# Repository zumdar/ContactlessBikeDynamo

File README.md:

# Contactless Bicycle Dynamo using Eddy Currents

This is a [certified Open Source](https://certification.oshwa.org/us002771.html) small electrical generator that creates enough current to power a small bicycle light while your wheel is spinning. 

# Description

The design files here include the physical design files for the Dynamo and the LED light, as well as a custom PCB for the LED light which is a simple voltage rectifier doubler and choice of red or white led. 

If you would like to make this project:
- print off the files in:
  -  \Mechanical\Components\STLs\Final STL
- acquire parts in the 
- aquire tools in the 
- follow instructions in the 

This project started off with a desire to be a workshop I could host to show an interesting way to generate electricity and power a bike light without needing a battery. 

Here are the workshop slides:
https://docs.google.com/presentation/d/1txSlyZcSNcTIk4scu_-NPuIz-HN-7od_rSDEqWW2YtM/edit?usp=sharing

# Technical 

## Physical Design Files
The parts are labelled as follows:

- P001-B100	-	Square Dynamo
- P001-B101	-	Dynamo Cover
- P001-B102	-	Magnet Holder Ring
- P001-B103	-	M5 Bearing Adaptor
- P001-B104	-	Fork Bracket
- P001-B105	-	PCB Cover
- P001-B106	-	LED Light Mount

There is also an assembly of the Dynamo labelled:

- P001-B001	-	Dynamo
## PCB Design files

The PCB contains red and white LEDs which can be selected by doing a solder bridge while assembling. 

You can't use both at the same time. If you solder both, only the Red LED will light (it has a lower forward voltage). 

The LED PCB design can be found in:
- \Electrical\Dyno_LED_PCB

# Acknowledgments

Thank you to:
Lucas Ray, Clara Caspard, and YJ Rodrigues for helping develop this! 

# License
This is an certified [open source project](https://certification.oshwa.org/us002771.html)!

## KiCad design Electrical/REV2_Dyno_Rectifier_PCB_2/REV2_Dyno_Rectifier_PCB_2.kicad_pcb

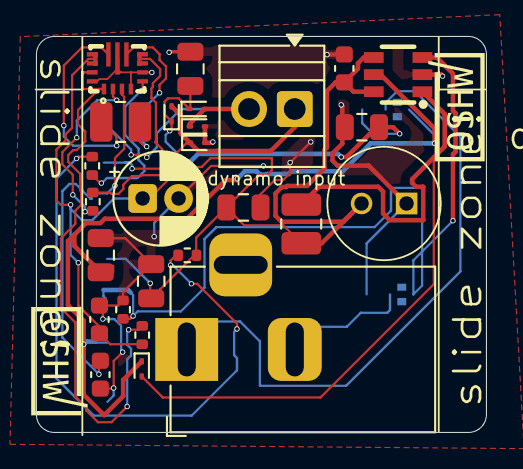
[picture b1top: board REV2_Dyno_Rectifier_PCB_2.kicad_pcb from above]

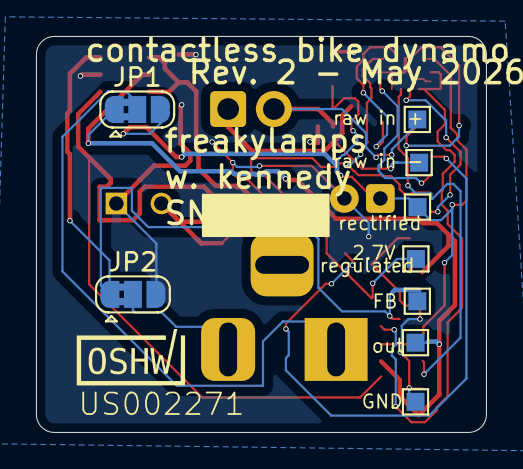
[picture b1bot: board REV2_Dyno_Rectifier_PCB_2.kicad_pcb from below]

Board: 2 copper layers, 25.0 x 22.0 mm, 35 parts (9 on the bottom side), 17 nets.

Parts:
C1: 100u; CP_Radial_D5.0mm_P2.00mm
C2, C8, C9, C10: 10uF; C_0805_2012Metric
C3, C5: 10uF; C_0603_1608Metric
C4: 100nF; C_0603_1608Metric
C6: 47uF; C_0805_2012Metric
C7: 1F - 2.7V; supercapacitor - 4mm diameter
D1, D2, D3, D4, D5: D_Schottky; D_SOD-923
J1: Dynamo Input; TerminalBlock_Xinya_XY308-2.54-2P_1x02_P2.54mm_Horizontal
J2: Barrel_Jack_MountingPin; BarrelJack_Horizontal
JP1, JP2: SolderJumper_3_Bridged12; SolderJumper-3_P1.3mm_Bridged2Bar12_RoundedPad1.0x1.5mm
L1: 1.5uH; L_1008_2520Metric
L2: 2.2uH; L_1008_2520Metric
R1: 10k; R_0402_1005Metric
R2: 360k; R_0402_1005Metric
R3: 150k; R_0402_1005Metric
R4: 100k; R_0402_1005Metric
R5: 1.8; R_0402_1005Metric
TP1, TP2, TP3, TP4, TP5, TP6, TP7: TestPoint; TestPoint_Pad_1.0x1.0mm
U1: TPS63070RNMR; TPS63070RNMR-2
U2: PAM2803AAF095; PAM2803_SOT-23-6_L2.9-W1.6-P0.95-LS2.8-BR

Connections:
2.7V: C5.1, C6.1, C7.1, C8.1, L2.1, R2.1, R4.1, TP4.1, U1.7 (Vout), U2.4 (SHDN#), U2.6 (VIN)
FB: JP2.1 (A), R5.1, TP5.1, U2.3 (FB)
GND: C1.2, C2.2, C3.2, C4.2, C5.2, C6.2, C7.2, C8.2, C9.2, C10.2, D1.2 (A), D2.2 (A), JP2.3 (B), R5.2, TP7.1, U1.4 (GND), U1.6 (FB2), U1.10 (PGND), U1.15 (Vsel), U2.2 (GND)
unnamed: D5.2 (A), L2.2, U2.1 (SW)
unnamed: R2.2, R3.1
unnamed: R1.2, U1.1 (PS/SYNC), U1.14 (EN)
unnamed: R3.2, U1.5 (FB)
unnamed: L1.1, U1.11 (L1)
unnamed: L1.2, U1.9 (L2)
unnamed: R4.2, U1.2 (PG)
unnamed: C4.1, U1.3 (Vaux)
Out_Sleeve: J2.2, JP2.2 (C)
Out_Tip: J2.1, JP1.2 (C)
Raw_Input_+: D1.1 (K), D3.2 (A), J1.2, TP1.1
Raw_Input_-: D2.1 (K), D4.2 (A), J1.1, TP2.1
Rectified: C1.1, C2.1, C3.1, C10.1, D3.1 (K), D4.1 (K), JP1.3 (B), R1.1, TP3.1, U1.12 (Vin)
V_out: C9.1, D5.1 (K), JP1.1 (A), TP6.1, U2.5 (VOUT)

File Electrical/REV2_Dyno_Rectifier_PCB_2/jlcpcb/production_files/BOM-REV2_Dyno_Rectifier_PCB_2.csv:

Comment,Designator,Footprint,LCSC,Quantity
1.5uH,L1,L_1008_2520Metric,C5339200,1
1.8,R5,R_0402_1005Metric,C2960794,1
100k,R4,R_0402_1005Metric,C25741,1
100nF,C4,C_0603_1608Metric,C14663,1
100u,C1,CP_Radial_D5.0mm_P2.00mm,C108360,1
10k,R1,R_0402_1005Metric,C25744,1
10uF,"C10,C2,C8,C9",C_0805_2012Metric,C440198,4
10uF,"C3,C5",C_0603_1608Metric,C96446,2
150k,R3,R_0402_1005Metric,C2909320,1
2.2uH,L2,L_1008_2520Metric,C394950,1
360k,R2,R_0402_1005Metric,C2909351,1
47uF,C6,C_0805_2012Metric,C16780,1
Barrel_Jack_MountingPin,J2,BarrelJack_Horizontal,C16214,1
D_Schottky,"D1,D2,D3,D4,D5",D_SOD-923,C2886012,5
Dynamo Input,J1,TerminalBlock_Xinya_XY308-2.54-2P_1x02_P2.54mm_Horizontal,C557685,1
PAM2803AAF095,U2,PAM2803_SOT-23-6_L2.9-W1.6-P0.95-LS2.8-BR,C55801,1
TPS63070RNMR,U1,TPS63070RNMR-2,C109322,1
1F - 2.7V,C7,supercapacitor - 4mm diameter,,1

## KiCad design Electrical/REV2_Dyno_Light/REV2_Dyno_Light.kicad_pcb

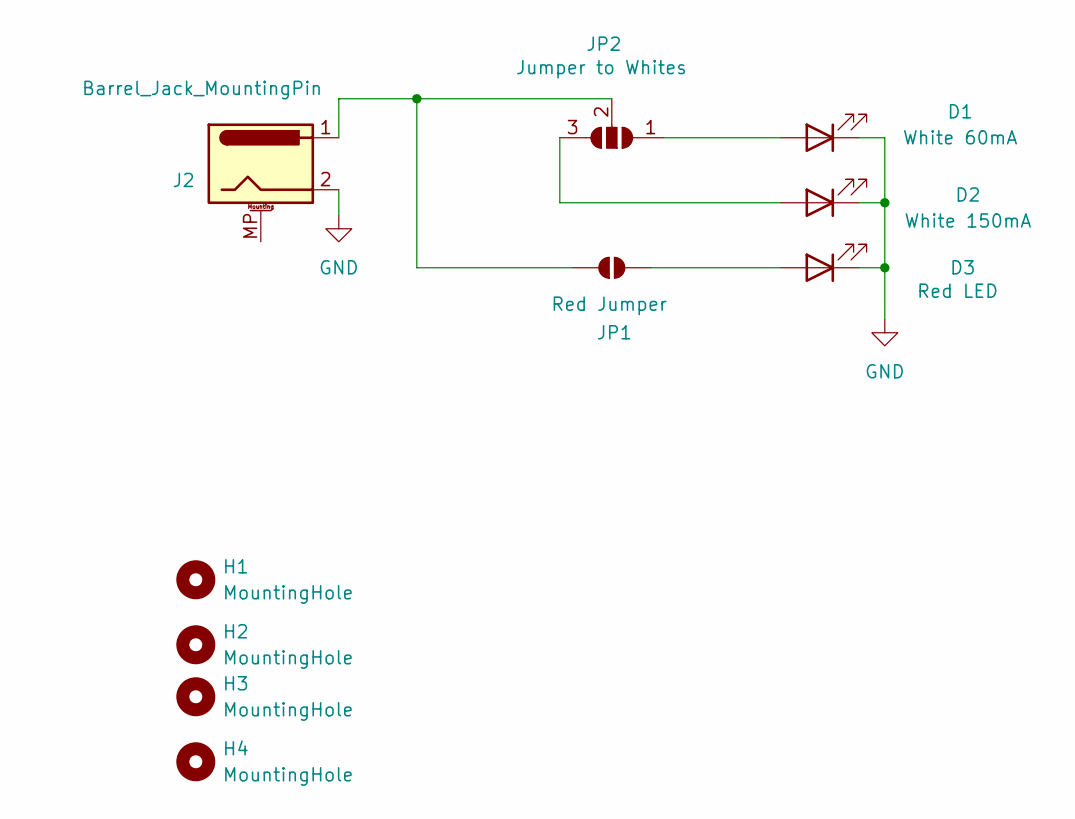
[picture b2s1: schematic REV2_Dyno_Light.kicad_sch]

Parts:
D1: White 60mA; LED_PLCC_2835; LCSC C210310
D2: White 150mA; LED_PLCC_2835; LCSC C210320
D3: Red LED; LED_PLCC_2835
H1, H2, H3, H4: MountingHole; MountingHole_3.2mm_M3
J2: Barrel_Jack_MountingPin; BarrelJack_Horizontal; LCSC C16214
JP1: Red Jumper; SolderJumper-2_P1.3mm_Open_TrianglePad1.0x1.5mm
JP2: Jumper to Whites; SolderJumper-3_P2.0mm_Open_TrianglePad1.0x1.5mm_NumberLabels

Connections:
GND: D1.1 (K), D2.1 (K), D3.1 (K), J2.2
unnamed: D1.2 (A), JP2.1 (A)
unnamed: D2.2 (A), JP2.3 (B)
unnamed: D3.2 (A), JP1.2 (B)
unnamed: J2.1, JP1.1 (A), JP2.2 (C)

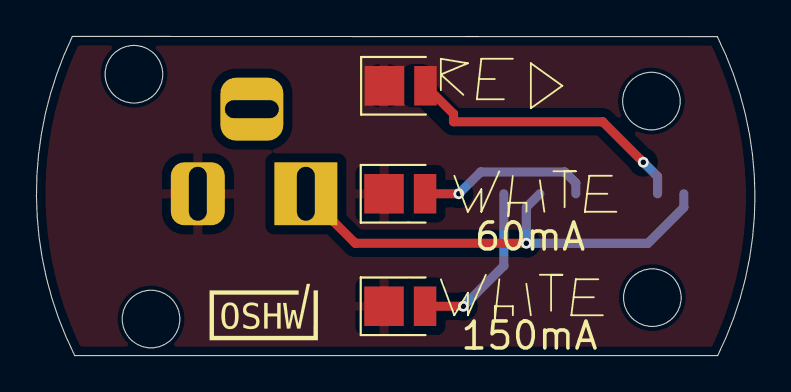
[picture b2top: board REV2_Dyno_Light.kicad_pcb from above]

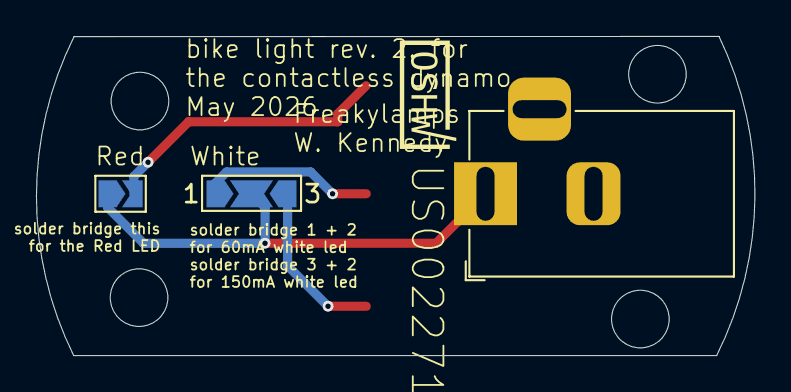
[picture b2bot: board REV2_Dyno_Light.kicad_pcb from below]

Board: 2 copper layers, 39.9 x 17.7 mm, 10 parts (3 on the bottom side), 5 nets.

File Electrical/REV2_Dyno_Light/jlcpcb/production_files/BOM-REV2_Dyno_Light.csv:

Comment,Designator,Footprint,LCSC,Quantity
Barrel_Jack_MountingPin,J2,BarrelJack_Horizontal,C16214,1
White 150mA,D2,LED_PLCC_2835,C210320,1
White 60mA,D1,LED_PLCC_2835,C210310,1
Red LED,D3,LED_PLCC_2835,,1

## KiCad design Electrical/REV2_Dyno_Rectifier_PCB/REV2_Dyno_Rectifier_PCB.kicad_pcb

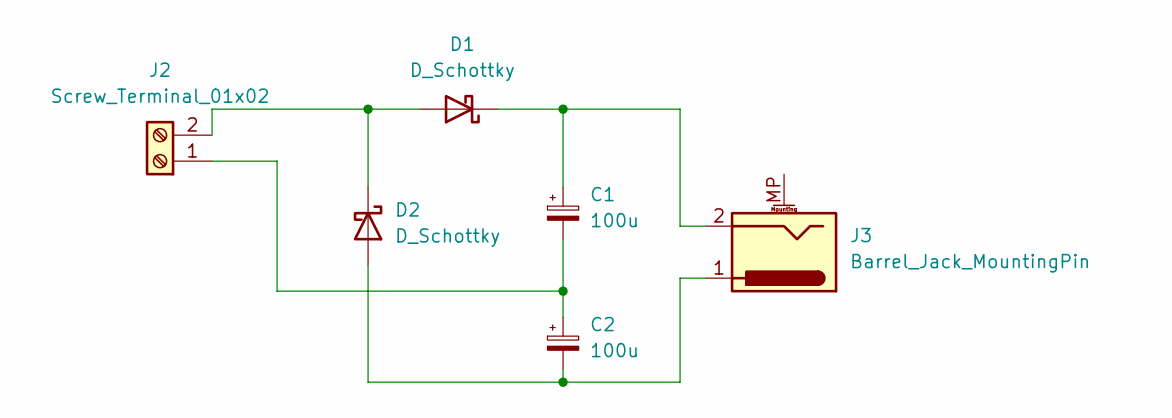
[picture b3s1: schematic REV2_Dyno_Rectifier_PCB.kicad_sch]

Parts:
C1, C2: 100u; CP_Elec_6.3x7.7; LCSC C3338
D1, D2: D_Schottky; D_SOD-123; LCSC C8570
J2: Screw_Terminal_01x02; TerminalBlock_Xinya_XY308-2.54-2P_1x02_P2.54mm_Horizontal; LCSC C557685
J3: Barrel_Jack_MountingPin; BarrelJack_Horizontal; LCSC C16214

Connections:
unnamed: D1.2 (A), D2.1 (K), J2.2
unnamed: C1.1, D1.1 (K), J3.2
unnamed: C2.2, D2.2 (A), J3.1
unnamed: C1.2, C2.1, J2.1

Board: 2 copper layers, 6 parts (0 on the bottom side), 4 nets, no tracks yet.

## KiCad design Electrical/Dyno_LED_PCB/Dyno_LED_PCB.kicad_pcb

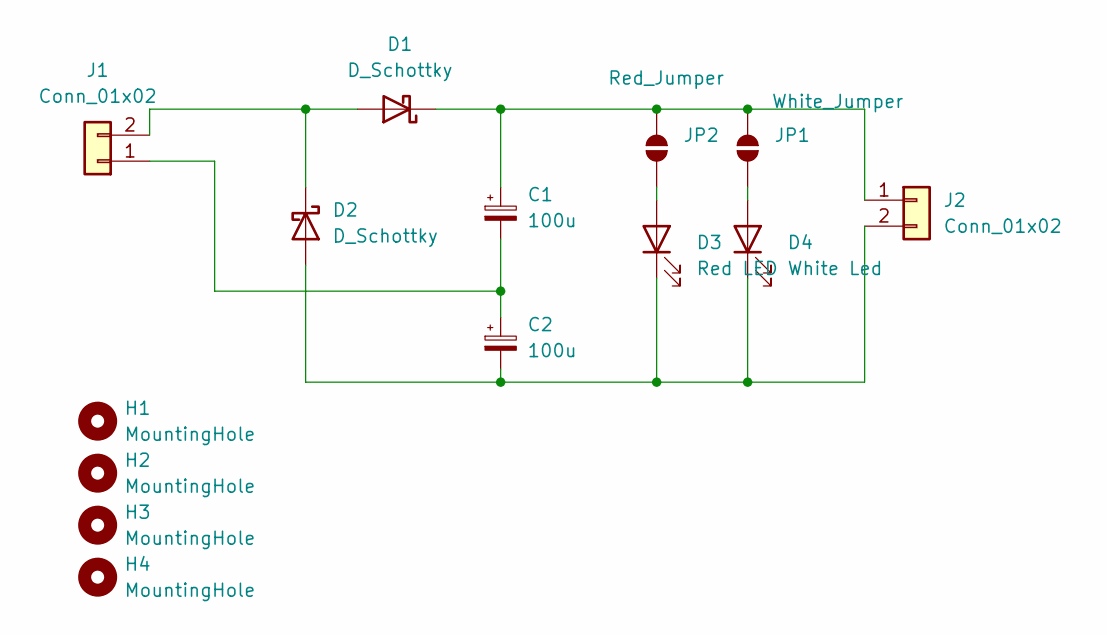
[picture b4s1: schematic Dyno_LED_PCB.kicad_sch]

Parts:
C1, C2: 100u; CP_Elec_6.3x7.7
D1, D2: D_Schottky; D_SOD-123
D3: Red LED; LED_1206_3216Metric
D4: White Led; LED_1206_3216Metric
H1, H2, H3, H4: MountingHole; MountingHole_2.2mm_M2
J1: Conn_01x02; JST_XH_B2B-XH-A_1x02_P2.50mm_Vertical
J2: Conn_01x02; PinHeader_1x02_P2.54mm_Vertical
JP1: White_Jumper; SolderJumper-2_P1.3mm_Open_RoundedPad1.0x1.5mm
JP2: Red_Jumper; SolderJumper-2_P1.3mm_Open_RoundedPad1.0x1.5mm

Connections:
unnamed: D1.2 (A), D2.1 (K), J1.2
unnamed: C1.1, D1.1 (K), J2.1, JP1.2 (B), JP2.2 (B)
unnamed: C2.2, D2.2 (A), D3.1 (K), D4.1 (K), J2.2
unnamed: D3.2 (A), JP2.1 (A)
unnamed: D4.2 (A), JP1.1 (A)
unnamed: C1.2, C2.1, J1.1

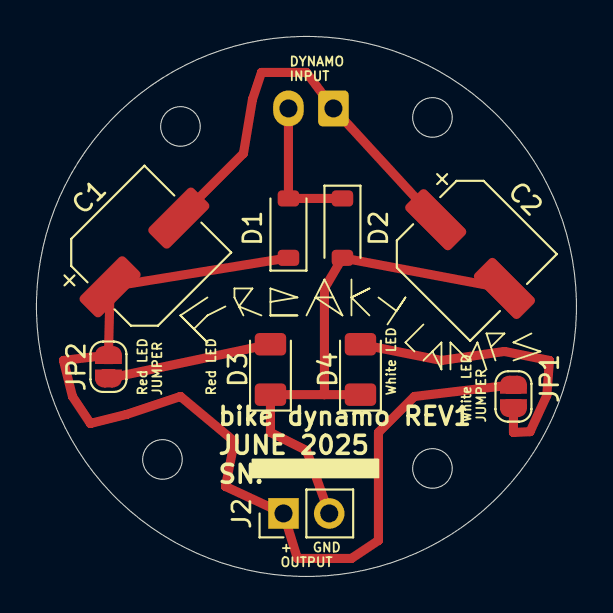
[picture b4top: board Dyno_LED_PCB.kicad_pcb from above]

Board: 2 copper layers, 30.0 x 30.0 mm, 14 parts (1 on the bottom side), 6 nets.

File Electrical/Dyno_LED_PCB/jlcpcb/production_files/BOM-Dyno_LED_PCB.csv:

Comment,Designator,Footprint,LCSC
White Led,D4,LED_1206_3216Metric,C71796
Red LED,D3,LED_1206_3216Metric,C3646938
Conn_01x02,J2,PinHeader_1x02_P2.54mm_Vertical,
Conn_01x02,J1,JST_XH_B2B-XH-A_1x02_P2.50mm_Vertical,
D_Schottky,D2,D_SOD-123,C8570
D_Schottky,D1,D_SOD-123,C8570
100u,C2,CP_Elec_6.3x7.7,C3338
100u,C1,CP_Elec_6.3x7.7,C3338

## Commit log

2025-08-13 adding readme, more documentation
2025-08-13 updating readme
2025-08-13 adding bill of materials, updating readme
2025-08-13 made BOM into CSV files instead of a google sheet
2025-08-15 adding license file and adding license facts to readme
2026-04-14 starting to work on V2 design files
2026-04-14 restore V2 design files after rebase mishap
2026-04-16 Add certification details to README
    Updated README to include certification information for the project.
2026-05-01 rev 2 circuit basically done, board almost laid out, also mechanical updates
2026-05-01 schematic should be done! component placement almost done
2026-05-04 sent off rectifier PCB and the Light PCB off to JLCPCB tonight
2026-05-19 V2 is (pretty much) done! need to organize things better but it is all here!
2026-05-26 cleaning up documentation a little bit
